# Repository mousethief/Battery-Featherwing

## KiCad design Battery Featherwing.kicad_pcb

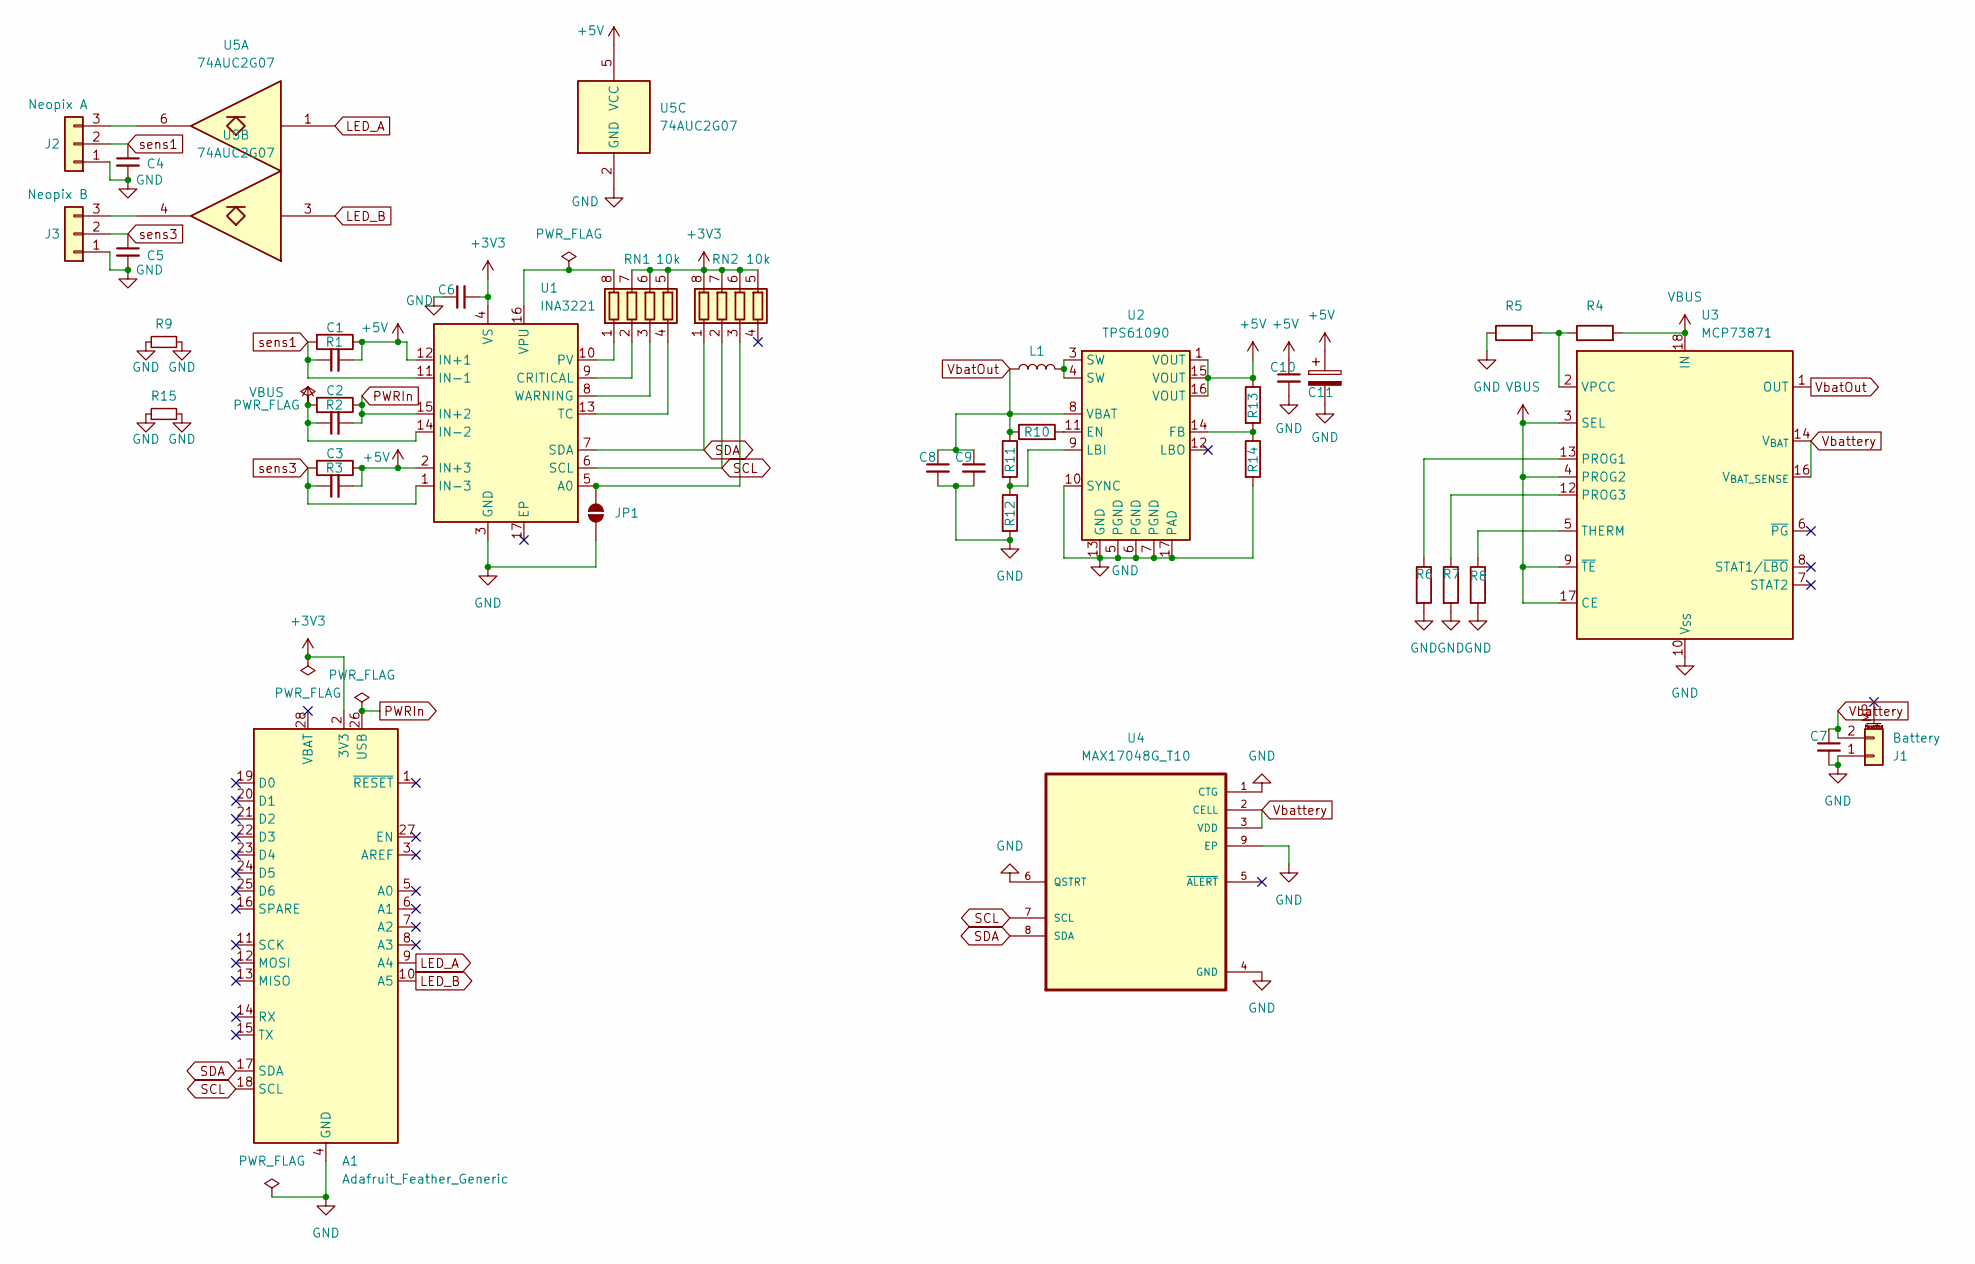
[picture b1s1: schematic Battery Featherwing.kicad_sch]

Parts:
A1: Adafruit_Feather_Generic; Adafruit_Feather_WithMountingHoles
C1, C2, C3, C6, C9: 0.1uF; C_0402_1005Metric
C4, C5: 100uF; C_0402_1005Metric
C7, C8: 10uF; C_0402_1005Metric
C10: 2.2uF; C_0402_1005Metric
C11: 100uF; C_0805_2012Metric
J1: Battery; JST_PH_B2B-PH-SM4-TB_1x02-1MP_P2.00mm_Vertical
J2: Neopix A; JST_PH_B3B-PH-K_1x03_P2.00mm_Vertical
J3: Neopix B; JST_PH_B3B-PH-K_1x03_P2.00mm_Vertical
JP1: SolderJumper_2_Open; SolderJumper-2_P1.3mm_Open_TrianglePad1.0x1.5mm
L1: 6.8uH; L_6.3x6.3_H3
R1, R2, R3: 0.1; R_2512_6332Metric
R4: 270k; R_0402_1005Metric
R5, R7: 100k; R_0402_1005Metric
R6: 1.0k; R_0402_1005Metric
R8: 16k; R_0402_1005Metric
R9, R15: 0; R_1206_3216Metric
R10, R14: 200k; R_0402_1005Metric
R11, R13: 1.87M; R_0402_1005Metric
R12: 340k; R_0402_1005Metric
RN1, RN2: 10k; R_Array_Convex_4x0612
U1: INA3221; Texas_RGV0016A_VQFN-16-1EP_4x4mm_P0.65mm_EP2.1x2.1mm
U2: TPS61090; Texas_RSA_VQFN-16-1EP_4x4mm_P0.65mm_EP2.7x2.7mm_ThermalVias
U3: MCP73871; QFN-20-1EP_4x4mm_P0.5mm_EP2.5x2.5mm
U4: MAX17048G_T10; SON50P200X200X80-9N
U5: 74AUC2G07; TSOP-6_1.65x3.05mm_P0.95mm

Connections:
+3V3: A1.2 (3V3), C6.2, RN1.5 (R4.2), RN1.6 (R3.2), RN1.7 (R2.2), RN2.5 (R4.2), RN2.6 (R3.2), RN2.7 (R2.2), RN2.8 (R1.2), U1.4 (VS)
+5V: C1.2, C3.2, C10.1, C11.1, R1.1, R3.1, R13.1, U1.2 (IN+3), U1.12 (IN+1), U2.1 (VOUT), U2.15 (VOUT), U2.16 (VOUT), U5.5 (VCC)
GND: A1.4 (GND), C4.2, C5.2, C6.1, C7.2, C8.2, C9.2, C10.2, C11.2, J1.1, J2.1, J3.1, JP1.1 (A), R5.1, R6.2, R7.2, R8.2, R9.1, R9.2, R12.2, R14.2, R15.1, R15.2, U1.3 (GND), U2.5 (PGND), U2.6 (PGND), U2.7 (PGND), U2.10 (SYNC), U2.13 (GND), U2.17 (PAD), U3.10 (V_{SS}), U3.11 (V_{SS}), U3.21 (V_{SS}), U4.1 (CTG), U4.4 (GND), U4.6 (QSTRT), U4.9 (EP), U5.2 (GND)
LED_A: A1.9 (A4), U5.1
LED_B: A1.10 (A5), U5.3
unnamed: J2.3, U5.6
unnamed: J3.3, U5.4
unnamed: JP1.2 (B), RN2.3 (R3.1), U1.5 (A0)
unnamed: L1.2, U2.3 (SW), U2.4 (SW)
unnamed: RN1.1 (R1.1), U1.10 (PV)
unnamed: RN1.8 (R1.2), U1.16 (VPU)
unnamed: RN1.2 (R2.1), U1.9 (CRITICAL)
unnamed: RN1.3 (R3.1), U1.8 (WARNING)
unnamed: RN1.4 (R4.1), U1.13 (TC)
unnamed: R10.2, U2.11 (EN)
unnamed: R13.2, R14.1, U2.14 (FB)
unnamed: R11.2, R12.1, U2.9 (LBI)
unnamed: R6.1, U3.13 (PROG1)
unnamed: R7.1, U3.12 (PROG3)
unnamed: R8.1, U3.5 (THERM)
unnamed: R4.1, R5.2, U3.2 (VPCC)
PWRIn: A1.26 (USB), C2.2, R2.1, U1.15 (IN+2)
SCL: A1.18 (SCL), RN2.2 (R2.1), U1.6 (SCL), U4.7 (SCL)
SDA: A1.17 (SDA), RN2.1 (R1.1), U1.7 (SDA), U4.8 (SDA)
VBUS: C2.1, R2.2, R4.2, U1.14 (IN-2), U3.3 (SEL), U3.4 (PROG2), U3.9 (~TE), U3.17 (CE), U3.18 (IN), U3.19 (IN)
VbatOut: C8.1, C9.1, L1.1, R10.1, R11.1, U2.8 (VBAT), U3.1 (OUT), U3.20 (OUT)
Vbattery: C7.1, J1.2, U3.14 (V_{BAT}), U3.15 (V_{BAT}), U3.16 (V_{BAT_SENSE}), U4.2 (CELL), U4.3 (VDD)
sens1: C1.1, C4.1, J2.2, R1.2, U1.11 (IN-1)
sens3: C3.1, C5.1, J3.2, R3.2, U1.1 (IN-3)

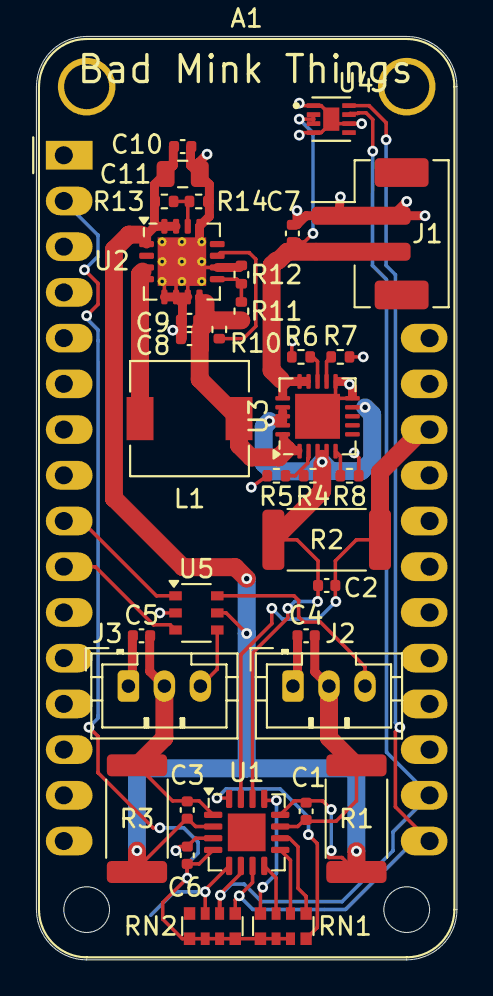
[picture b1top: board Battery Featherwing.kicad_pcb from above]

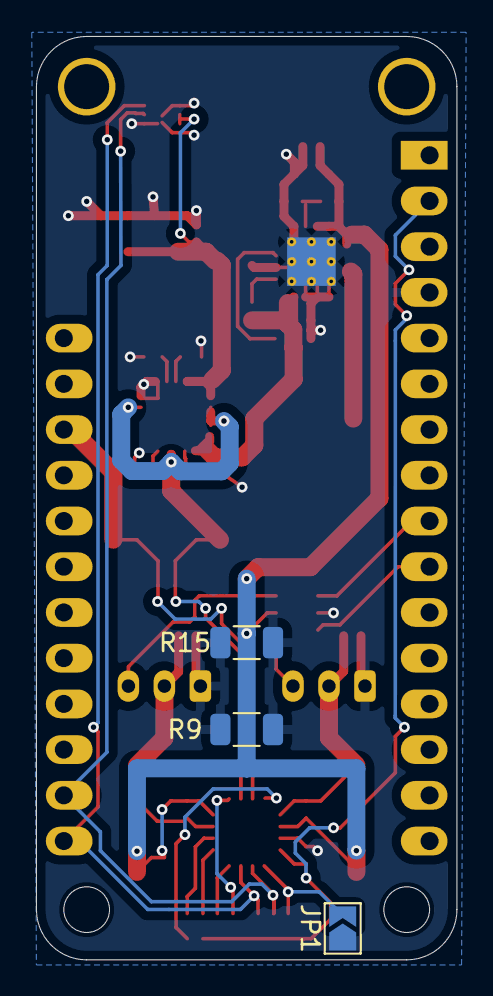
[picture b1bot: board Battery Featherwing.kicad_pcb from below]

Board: 2 copper layers, 23.4 x 51.3 mm, 39 parts (3 on the bottom side), 29 nets.

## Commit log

2024-10-05 Initial commit. Done, but should be done More Better. Do it.
2024-10-05 Added some text to the board, for practice.
